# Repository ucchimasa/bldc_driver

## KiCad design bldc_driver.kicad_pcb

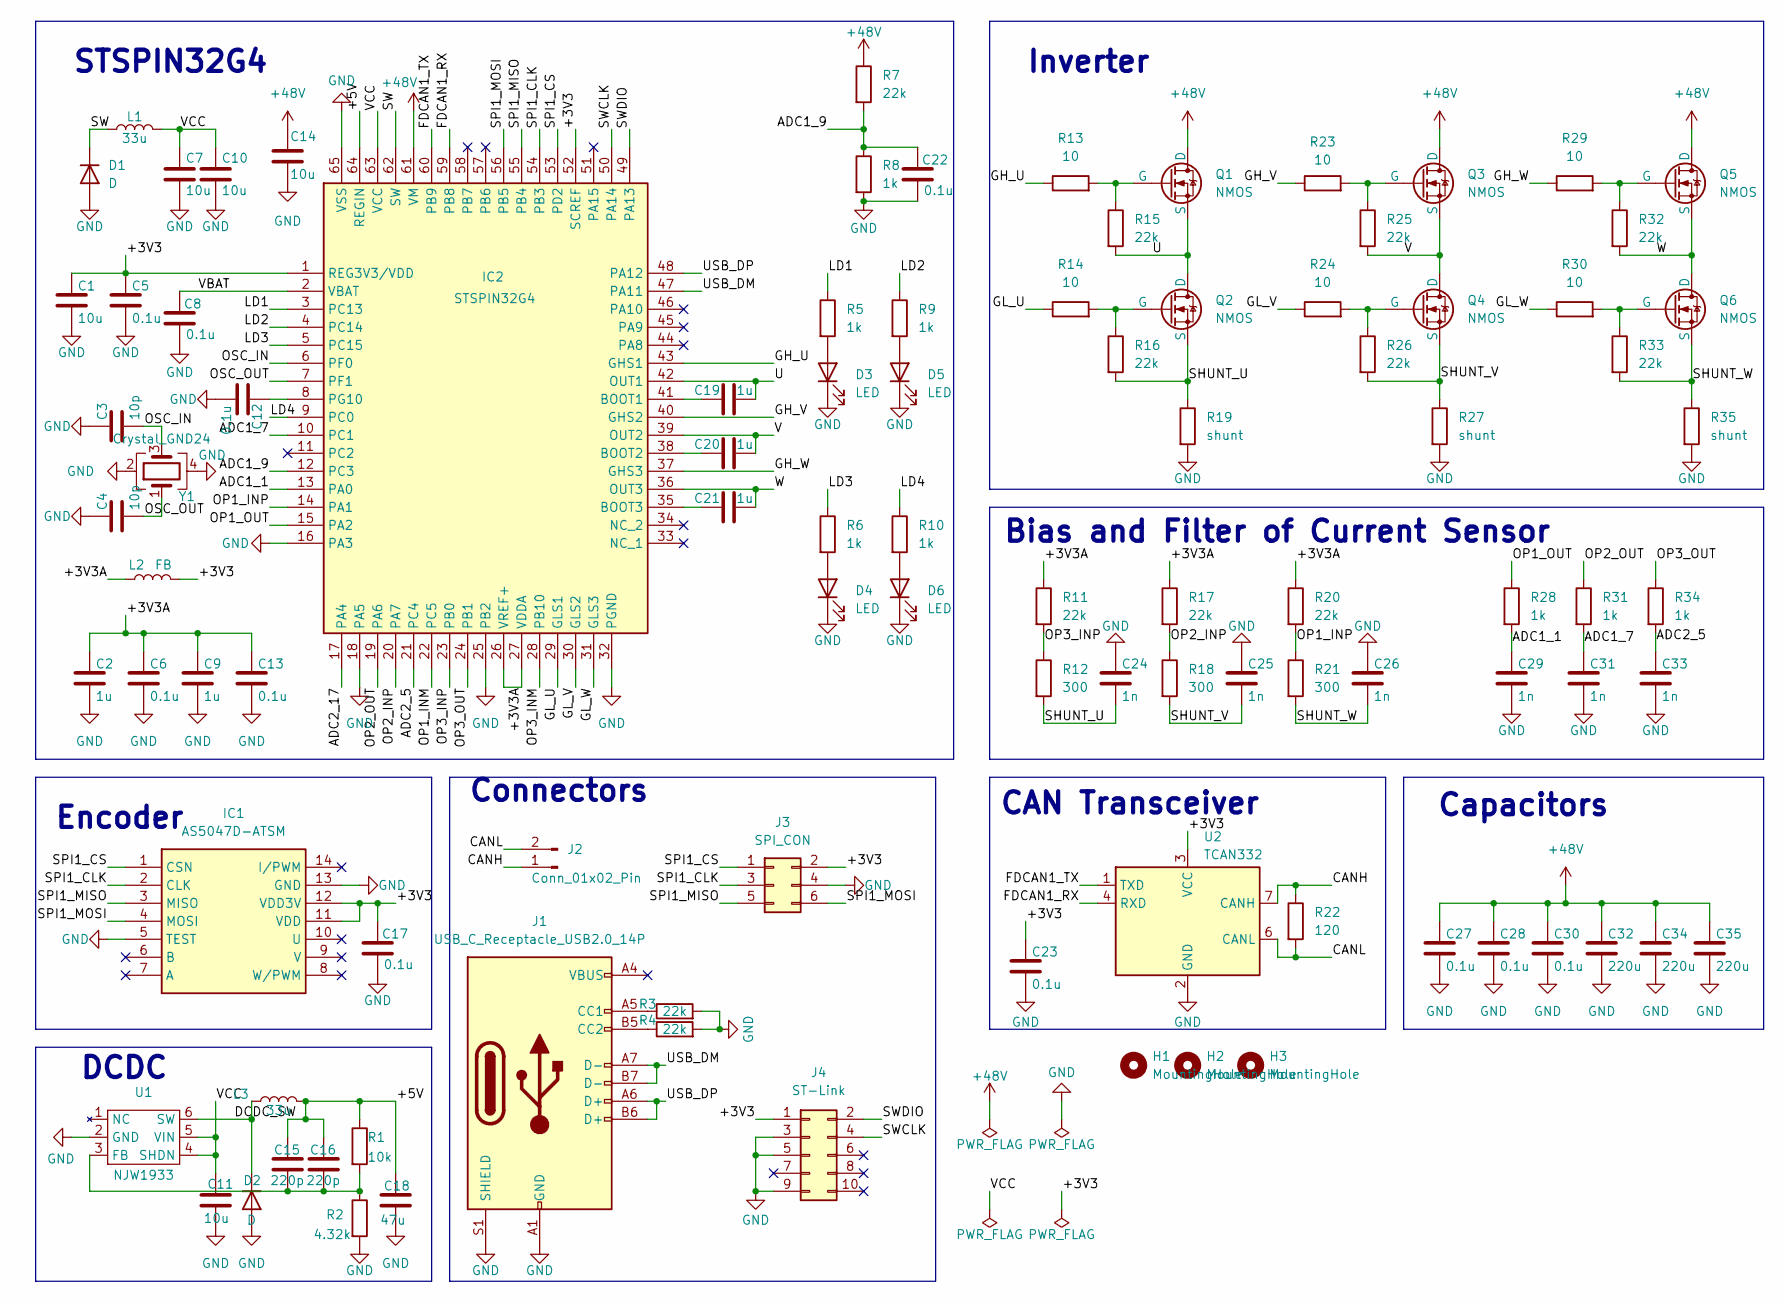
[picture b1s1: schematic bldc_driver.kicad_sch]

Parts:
C1, C14: 10u; C_1206_3216Metric_Pad1.33x1.80mm_HandSolder
C2, C9, C19, C20, C21: 1u; C_0603_1608Metric_Pad1.08x0.95mm_HandSolder
C3, C4: 10p; C_0603_1608Metric_Pad1.08x0.95mm_HandSolder
C5, C6, C8, C12, C13, C17, C22, C23, C27, C28, C30: 0.1u; C_0603_1608Metric_Pad1.08x0.95mm_HandSolder
C7, C10, C11: 10u; C_0805_2012Metric_Pad1.18x1.45mm_HandSolder
C15, C16: 220p; C_0402_1005Metric_Pad0.74x0.62mm_HandSolder
C18: 47u; C_1210_3225Metric_Pad1.33x2.70mm_HandSolder
C24, C25, C26, C29, C31, C33: 1n; C_0603_1608Metric_Pad1.08x0.95mm_HandSolder
C32, C34, C35: 220u; CP_Elec_10x10
D1, D2: D; RSX101VAM
D3, D4, D5, D6: LED; D_0603_1608Metric_Pad1.05x0.95mm_HandSolder
H1, H2, H3: MountingHole; MountingHole_3.2mm_M3
IC1: AS5047D-ATSM; SOP65P640X120-14N; Mouser Part Number 985-AS5047D-ATSM
IC2: STSPIN32G4; QFN50P900X900X100-65N-D-padlong; Manufacturer_Part_Number STSPIN32G4
J1: USB_C_Receptacle_USB2.0_14P; USB_C_Receptacle_XKB_U262-16XN-4BVC11
J2: Conn_01x02_Pin; PinHeader_1x02_P2.54mm_Vertical
J3: SPI_CON; PinHeader_2x03_P2.54mm_Vertical
J4: ST-Link; PinHeader_2x05_P1.27mm_Vertical_big
L1, L3: 33u; ELL6SH330M
L2: FB; L_0603_1608Metric_Pad1.05x0.95mm_HandSolder
Q1, Q2, Q3, Q4, Q5, Q6: NMOS; SOT8002-1-8
R1: 10k; R_0603_1608Metric_Pad0.98x0.95mm_HandSolder
R2: 4.32k; R_0603_1608Metric_Pad0.98x0.95mm_HandSolder
R3, R4, R7, R11, R15, R16, R17, R20, R25, R26, R32, R33: 22k; R_0603_1608Metric_Pad0.98x0.95mm_HandSolder
R5, R6, R8, R9, R10, R28, R31, R34: 1k; R_0603_1608Metric_Pad0.98x0.95mm_HandSolder
R12, R18, R21: 300; R_0603_1608Metric_Pad0.98x0.95mm_HandSolder
R13, R14, R23, R24, R29, R30: 10; R_0603_1608Metric_Pad0.98x0.95mm_HandSolder
R19, R27, R35: shunt; R_2512_6332Metric_Pad1.40x3.35mm_HandSolder
R22: 120; R_0603_1608Metric_Pad0.98x0.95mm_HandSolder
U1: NJW1933; SOT-23-6-1
U2: TCAN332; SOIC-8_3.9x4.9mm_P1.27mm
Y1: Crystal_GND24; Crystal_SMD_SeikoEpson_FA238V-4Pin_3.2x2.5mm

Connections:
+48V: C14.1, C27.1, C28.1, C30.1, C32.1, C34.1, C35.1, IC2.61 (VM), Q1.1 (D), Q3.1 (D), Q5.1 (D), R7.1
/+3V3: C1.1, C5.1, C17.1, C23.1, IC1.11 (VDD), IC1.12 (VDD3V), IC2.1 (REG3V3/VDD), IC2.52 (SCREF), J3.2, J4.1, L2.2, U2.3 (VCC)
/+3V3A: C2.1, C6.1, C9.1, C13.1, IC2.26 (VREF+), IC2.27 (VDDA), L2.1, R11.1, R17.1, R20.1
/+5V: C15.1, C16.1, C18.1, IC2.64 (REGIN), L3.2, R1.1
/ADC1_1: C29.1, IC2.13 (PA0), R28.2
/ADC1_7: C31.1, IC2.10 (PC1), R31.2
/ADC1_9: C22.1, IC2.12 (PC3), R7.2, R8.1
/ADC2_5: C33.1, IC2.21 (PC4), R34.2
/ADC2_17: IC2.17 (PA4)
/CANH: J2.1, R22.1, U2.7 (CANH)
/CANL: J2.2, R22.2, U2.6 (CANL)
/DCDC_SW: D2.1 (K), L3.1, U1.6 (SW)
/FDCAN1_RX: IC2.59 (PB8), U2.4 (RXD)
/FDCAN1_TX: IC2.60 (PB9), U2.1 (TXD)
/GH_U: IC2.43 (GHS1), R13.1
/GH_V: IC2.40 (GHS2), R23.1
/GH_W: IC2.37 (GHS3), R29.1
/GL_U: IC2.29 (GLS1), R14.1
/GL_V: IC2.30 (GLS2), R24.1
/GL_W: IC2.31 (GLS3), R30.1
/LD1: IC2.3 (PC13), R5.1
/LD2: IC2.4 (PC14), R9.1
/LD3: IC2.5 (PC15), R6.1
/LD4: IC2.9 (PC0), R10.1
/OP1_INM: IC2.22 (PC5)
/OP1_INP: IC2.14 (PA1), R20.2, R21.1
/OP1_OUT: IC2.15 (PA2), R28.1
/OP2_INP: IC2.20 (PA7), R17.2, R18.1
/OP2_OUT: IC2.19 (PA6), R31.1
/OP3_INM: IC2.28 (PB10)
/OP3_INP: IC2.23 (PB0), R11.2, R12.1
/OP3_OUT: IC2.24 (PB1), R34.1
/OSC_IN: C3.2, IC2.6 (PF0), Y1.3
/OSC_OUT: C4.2, IC2.7 (PF1), Y1.1
/SHUNT_U: C24.2, Q2.3 (S), R12.2, R16.2, R19.1
/SHUNT_V: C25.2, Q4.3 (S), R18.2, R26.2, R27.1
/SHUNT_W: C26.2, Q6.3 (S), R21.2, R33.2, R35.1
/SPI1_CLK: IC1.2 (CLK), IC2.54 (PB3), J3.3
/SPI1_CS: IC1.1 (CSN), IC2.53 (PD2), J3.1
/SPI1_MISO: IC1.3 (MISO), IC2.55 (PB4), J3.5
/SPI1_MOSI: IC1.4 (MOSI), IC2.56 (PB5), J3.6
/SW: D1.1 (K), IC2.62 (SW), L1.1
/SWCLK: IC2.50 (PA14), J4.4
/SWDIO: IC2.49 (PA13), J4.2
/U: C19.2, IC2.42 (OUT1), Q1.3 (S), Q2.1 (D), R15.2
/USB_DM: IC2.47 (PA11), J1.A7 (D-), J1.B7 (D-)
/USB_DP: IC2.48 (PA12), J1.A6 (D+), J1.B6 (D+)
/V: C20.2, IC2.39 (OUT2), Q3.3 (S), Q4.1 (D), R25.2
/VBAT: C8.1, IC2.2 (VBAT)
/VCC: C7.1, C10.1, C11.1, IC2.63 (VCC), L1.2, U1.4 (SHDN), U1.5 (VIN)
/W: C21.2, IC2.36 (OUT3), Q5.3 (S), Q6.1 (D), R32.2
GND: C1.2, C2.2, C3.1, C4.1, C5.2, C6.2, C7.2, C8.2, C9.2, C10.2, C11.2, C12.2, C13.2, C14.2, C17.2, C18.2, C22.2, C23.2, C24.1, C25.1, C26.1, C27.2, C28.2, C29.2, C30.2, C31.2, C32.2, C33.2, C34.2, C35.2, D1.2 (A), D2.2 (A), D3.1 (K), D4.1 (K), D5.1 (K), D6.1 (K), IC1.5 (TEST), IC1.13 (GND), IC2.16 (PA3), IC2.18 (PA5), IC2.25 (PB2), IC2.32 (PGND), IC2.65 (VSS), J1.A1 (GND), J1.A12 (GND), J1.B1 (GND), J1.B12 (GND), J1.S1 (SHIELD), J3.4, J4.3, J4.5, J4.9, R2.2, R3.2, R4.2, R8.2, R19.2, R27.2, R35.2, U1.2 (GND), U2.2 (GND), Y1.2, Y1.4
unnamed: D3.2 (A), R5.2
unnamed: D4.2 (A), R6.2
unnamed: D5.2 (A), R9.2
unnamed: D6.2 (A), R10.2
unnamed: C19.1, IC2.41 (BOOT1)
unnamed: C20.1, IC2.38 (BOOT2)
unnamed: C21.1, IC2.35 (BOOT3)
unnamed: C12.1, IC2.8 (PG10)
unnamed: J1.A5 (CC1), R3.1
unnamed: J1.B5 (CC2), R4.1
unnamed: Q1.2 (G), R13.2, R15.1
unnamed: Q2.2 (G), R14.2, R16.1
unnamed: Q3.2 (G), R23.2, R25.1
unnamed: Q4.2 (G), R24.2, R26.1
unnamed: Q5.2 (G), R29.2, R32.1
unnamed: Q6.2 (G), R30.2, R33.1
unnamed: C15.2, C16.2, R1.2, R2.1, U1.3 (FB)

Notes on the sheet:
Inverter
CAN Transceiver
Bias and Filter of Current Sensor
STSPIN32G4
DCDC
Encoder
Connectors
Capacitors

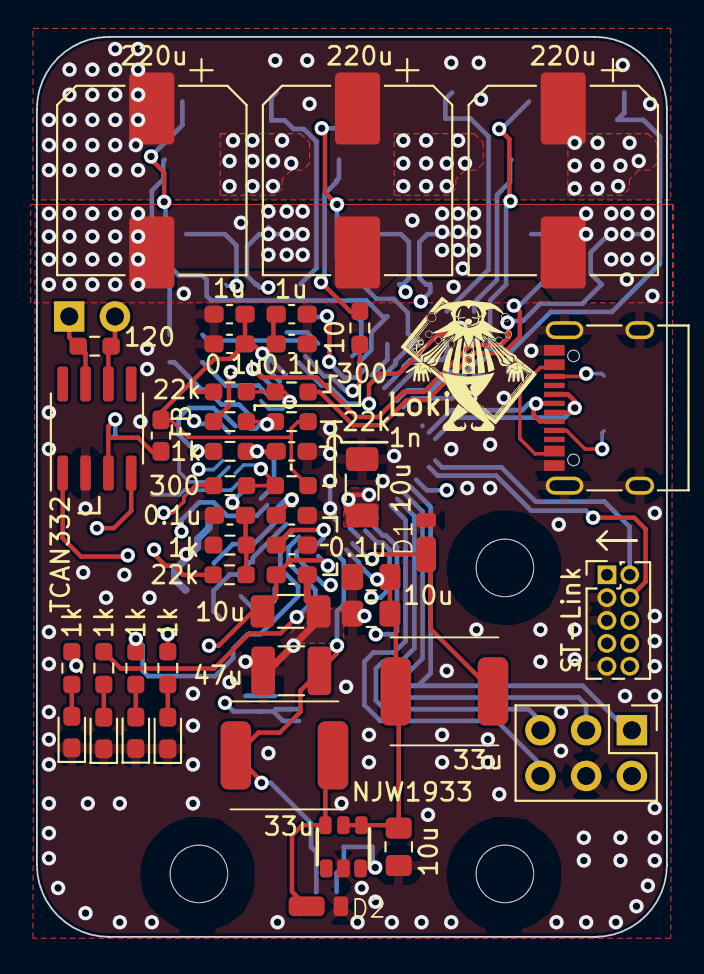
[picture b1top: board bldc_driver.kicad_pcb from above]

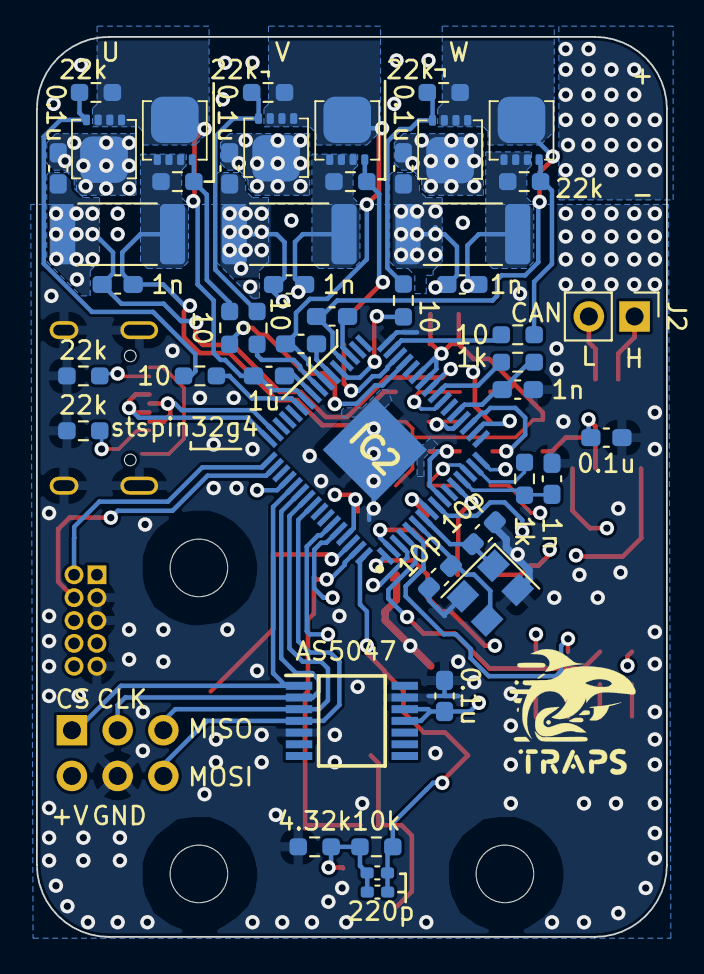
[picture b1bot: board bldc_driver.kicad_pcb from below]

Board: 4 copper layers, 35.0 x 50.0 mm, 97 parts (47 on the bottom side), 66 nets.

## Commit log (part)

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2024-11-24 回路図描いた
2024-11-26 フットプリント割り当て中
2024-11-28 割り当て終了+gitignore追加
2024-12-01 なんとなく配線できてきた
2024-12-02 配線がほとんど終わった
2024-12-09 ガーバー吐いた
2024-12-09 値及びフットプリント修正
